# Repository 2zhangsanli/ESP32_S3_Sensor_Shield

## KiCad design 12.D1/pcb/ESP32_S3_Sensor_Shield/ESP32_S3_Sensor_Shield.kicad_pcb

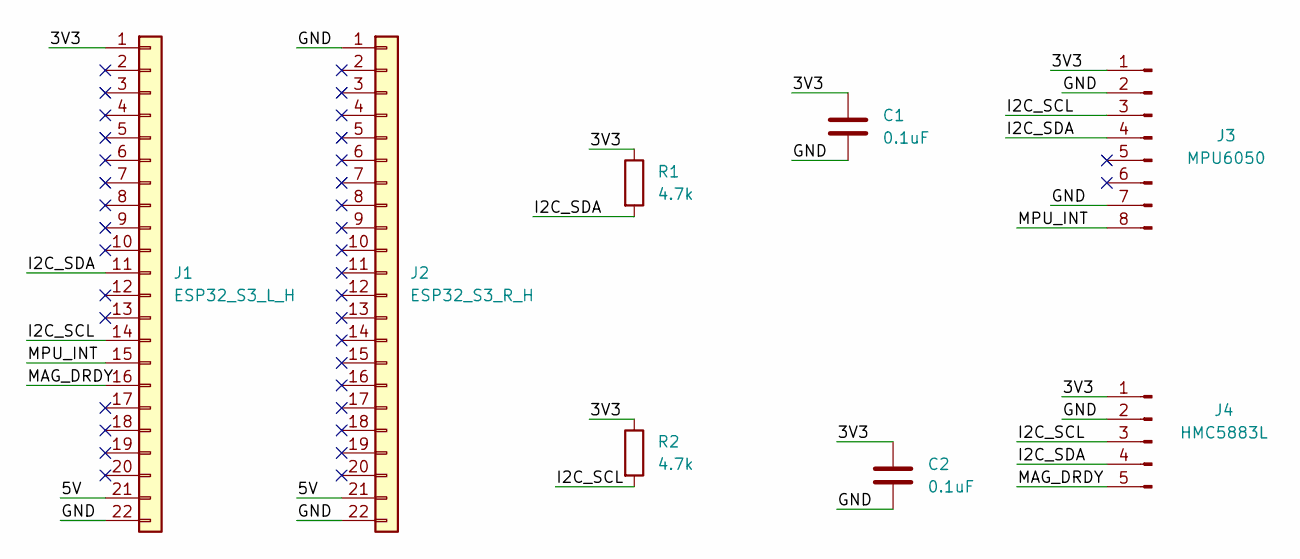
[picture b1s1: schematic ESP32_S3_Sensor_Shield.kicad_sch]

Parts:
C1, C2: 0.1uF; C_0805_2012Metric
J1: ESP32_S3_L_H; PinSocket_1x22_P2.54mm_Vertical
J2: ESP32_S3_R_H; PinSocket_1x22_P2.54mm_Vertical
J3: MPU6050; PinHeader_1x08_P2.54mm_Vertical
J4: HMC5883L; PinHeader_1x05_P2.54mm_Vertical
R1, R2: 4.7k; R_0805_2012Metric

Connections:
/3V3: C1.1, C2.1, J1.1, J3.1, J4.1, R1.1, R2.1
/5V: J1.21, J2.21
/GND: C1.2, C2.2, J1.22, J2.1, J2.22, J3.2, J3.7, J4.2
/I2C_SCL: J1.14, J3.3, J4.3, R2.2
/I2C_SDA: J1.11, J3.4, J4.4, R1.2
/MAG_DRDY: J1.16, J4.5
/MPU_INT: J1.15, J3.8

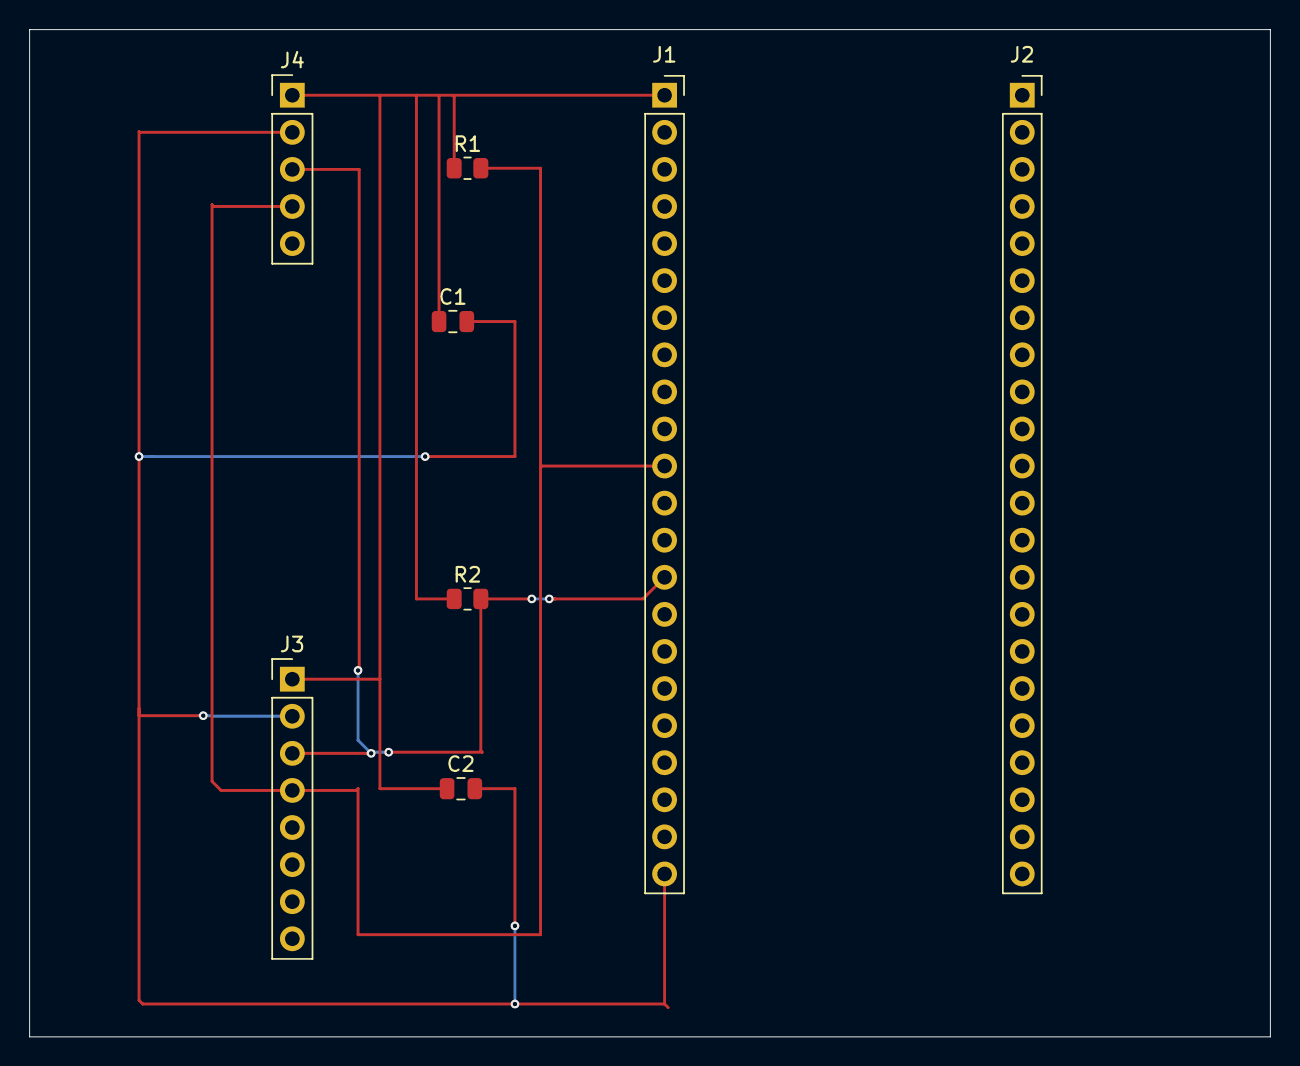
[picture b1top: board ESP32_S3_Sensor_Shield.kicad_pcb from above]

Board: 2 copper layers, 85.0 x 69.0 mm, 8 parts (0 on the bottom side), 7 nets.

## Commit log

2026-06-15 第12组 12.D1 ESP32-S3传感器板D1原理图完整工程
2026-06-16 完成12.D2全量交付文件归档： 1. D1存放KiCad PCB源工程，完成布线、铺铜、DRC校验 2. D2包含数据集data、预处理code、标定文档docs、PCB打板Gerber包prb_output、截图screenshots 全套硬件标定+人体识别数据文件整理完毕
2026-06-17 12.D1更新PCB原理图与配套文档；12.D2完成全套传感器标定： 1. 清理self_raw多余嵌套空目录； 2. 生成3被试6类人体活动raw/calibrated两套数据集； 3. 产出calib_params.json、标定报告.md、标定前后对比图； 4. 新增数据集生成、绘图Python脚本； 5. 清理zip压缩包、KiCad临时锁定文件。
2026-06-17 修复标定报告.md二进制编码损坏问题，重建纯文本标准Markdown报告
2026-06-17 补全12.D2全套缺失文件：3被试6类raw/calibrated数据集、标定对比图表、calib_params.json参数文件，完整归档D2全部标定交付项
2026-06-17 D3完整交付：信号预处理流水线、2.56s滑动窗口、时域频域特征提取、随机森林人体活动分类，包含预处理波形对比图、混淆矩阵、完整实验报告，实现Pipeline标准化防数据泄漏
2026-06-18 完成D4全部任务：时域+频域+跨传感器融合特征提取流水线，输出特征矩阵csv，配套特征字典文档，支持消融实验开关特征组
2026-06-27 上传项目总目录12，包含D1~D9全套代码与实训报告文档
